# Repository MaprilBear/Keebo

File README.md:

# Keebo - WIP
Successor/65% version of the [Keebi](https://github.com/MaprilBear/Keebi)

## Changes from the Keebi
- Slighty larger IPS display
- "63%" Layout
  - 65% but without INS/DEL, HOME/END, and PG UP/DN buttons
- Per-key RGB Lighting
- Volume Knob
- Improved Firmware
  - Programmable Macros
  - Media and Volume Controls

## Credits
Iterated upon from the [Keebi](https://github.com/MaprilBear/Keebi), a student project for UT Austin's ECE 445L class

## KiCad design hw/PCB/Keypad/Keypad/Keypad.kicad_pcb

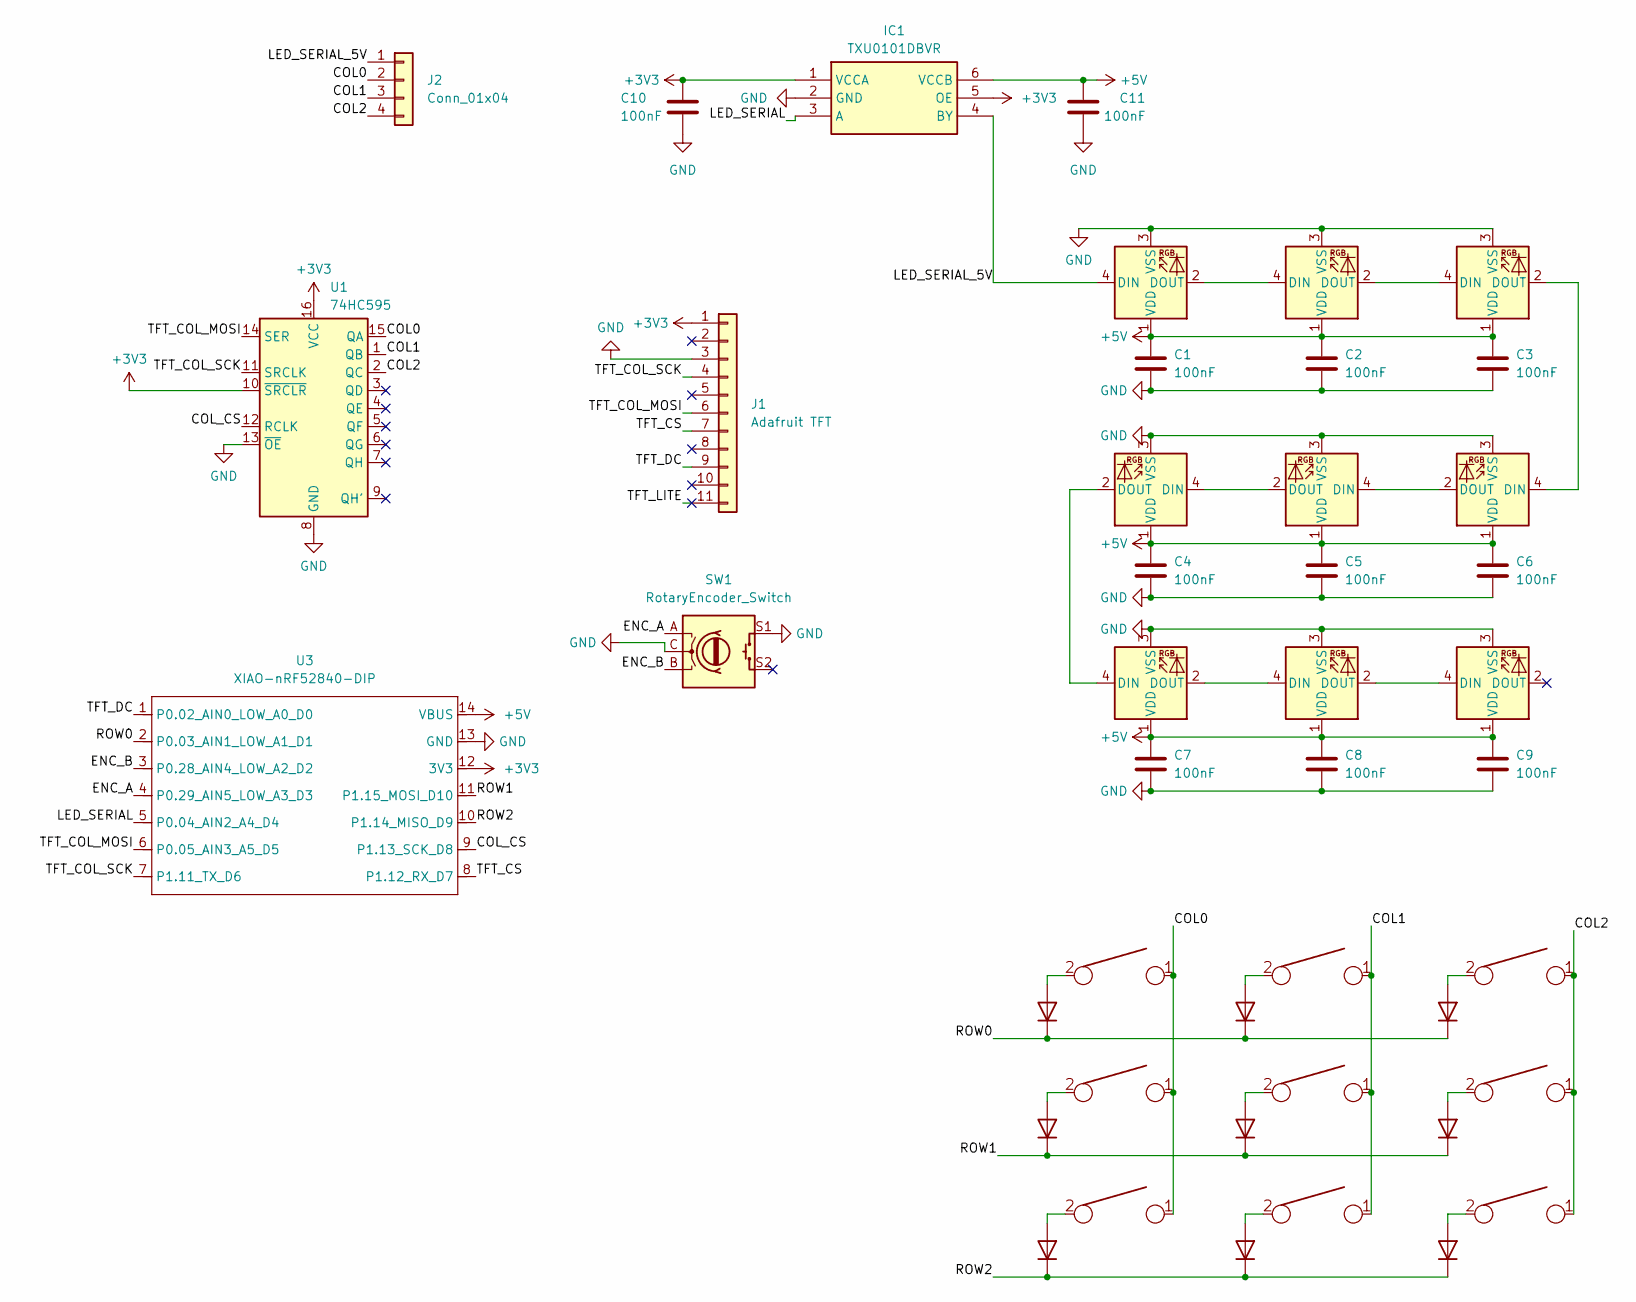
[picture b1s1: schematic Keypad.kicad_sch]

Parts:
C1, C2, C3, C4, C5, C6, C7, C8, C9, C10, C11: 100nF; C_0603_1608Metric
D1, D2, D3, D4, D5, D6, D7, D8, D9: 1N4448W; D_SOD-123
IC1: TXU0101DBVR; SOT-23-6; Mouser Part Number 595-TXU0101DCKR
J1: Adafruit TFT; Adafruit_1.47_TFT_Round_Rect
J2: Conn_01x04; PinHeader_1x04_P2.54mm_Vertical
K1, K2, K3, K4, K5, K6, K7, K8, K9: KEYSW; MX-Hotswap-1U
LED1, LED2, LED3, LED4, LED5, LED6, LED7, LED8, LED9: SK6812-MINI-E
SW1: RotaryEncoder_Switch; RollerEncoder_Panasonic_EVQWGD001
U1: 74HC595; TSSOP-16_4.4x5mm_P0.65mm
U3: XIAO-nRF52840-DIP

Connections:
+3V3: C10.1, IC1.1 (VCCA), IC1.5 (OE), J1.1, U1.10 (~SRCLR), U1.16 (VCC), U3.12 (3V3)
+5V: C1.1, C2.1, C3.1, C4.1, C5.1, C6.1, C7.1, C8.1, C9.1, C11.1, IC1.6 (VCCB), LED1.1 (VDD), LED2.1 (VDD), LED3.1 (VDD), LED4.1 (VDD), LED5.1 (VDD), LED6.1 (VDD), LED7.1 (VDD), LED8.1 (VDD), LED9.1 (VDD), U3.14 (VBUS)
/COL0: J2.2, K1.1, K6.1, K7.1, U1.15 (QA)
/COL1: J2.3, K2.1, K5.1, K8.1, U1.1 (QB)
/COL2: J2.4, K3.1, K4.1, K9.1, U1.2 (QC)
/COL_CS: U1.12 (RCLK), U3.9 (P1.13_SCK_D8)
/ENC_A: SW1.A, U3.4 (P0.29_AIN5_LOW_A3_D3)
/ENC_B: SW1.B, U3.3 (P0.28_AIN4_LOW_A2_D2)
/LED_SERIAL: IC1.3 (A), U3.5 (P0.04_AIN2_A4_D4)
/LED_SERIAL_5V: IC1.4 (BY), J2.1, LED1.4 (DIN)
/ROW0: D1.1 (K), D2.1 (K), D3.1 (K), U3.2 (P0.03_AIN1_LOW_A1_D1)
/ROW1: D4.1 (K), D5.1 (K), D6.1 (K), U3.11 (P1.15_MOSI_D10)
/ROW2: D7.1 (K), D8.1 (K), D9.1 (K), U3.10 (P1.14_MISO_D9)
/TFT_COL_MOSI: J1.6, U1.14 (SER), U3.6 (P0.05_AIN3_A5_D5)
/TFT_COL_SCK: J1.4, U1.11 (SRCLK), U3.7 (P1.11_TX_D6)
/TFT_CS: J1.7, U3.8 (P1.12_RX_D7)
/TFT_DC: J1.9, U3.1 (P0.02_AIN0_LOW_A0_D0)
/TFT_LITE: J1.11
GND: C1.2, C2.2, C3.2, C4.2, C5.2, C6.2, C7.2, C8.2, C9.2, C10.2, C11.2, IC1.2 (GND), J1.3, LED1.3 (VSS), LED2.3 (VSS), LED3.3 (VSS), LED4.3 (VSS), LED5.3 (VSS), LED6.3 (VSS), LED7.3 (VSS), LED8.3 (VSS), LED9.3 (VSS), SW1.C, SW1.S1, U1.8 (GND), U1.13 (~OE), U3.13 (GND)
unnamed: D1.2 (A), K1.2
unnamed: D2.2 (A), K2.2
unnamed: D3.2 (A), K3.2
unnamed: D4.2 (A), K6.2
unnamed: D5.2 (A), K5.2
unnamed: D6.2 (A), K4.2
unnamed: D7.2 (A), K7.2
unnamed: D8.2 (A), K8.2
unnamed: D9.2 (A), K9.2
unnamed: LED1.2 (DOUT), LED2.4 (DIN)
unnamed: LED2.2 (DOUT), LED3.4 (DIN)
unnamed: LED3.2 (DOUT), LED6.4 (DIN)
unnamed: LED4.4 (DIN), LED5.2 (DOUT)
unnamed: LED4.2 (DOUT), LED7.4 (DIN)
unnamed: LED5.4 (DIN), LED6.2 (DOUT)
unnamed: LED7.2 (DOUT), LED8.4 (DIN)
unnamed: LED8.2 (DOUT), LED9.4 (DIN)

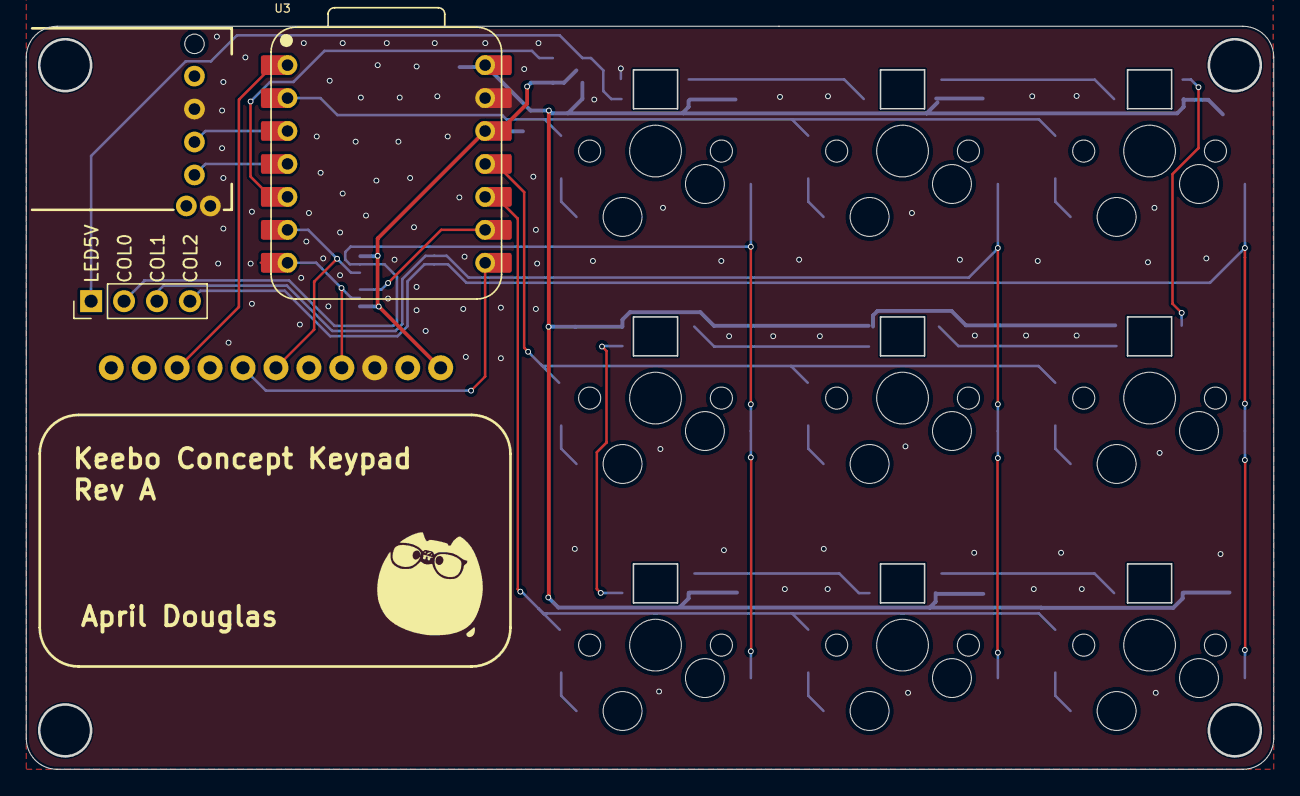
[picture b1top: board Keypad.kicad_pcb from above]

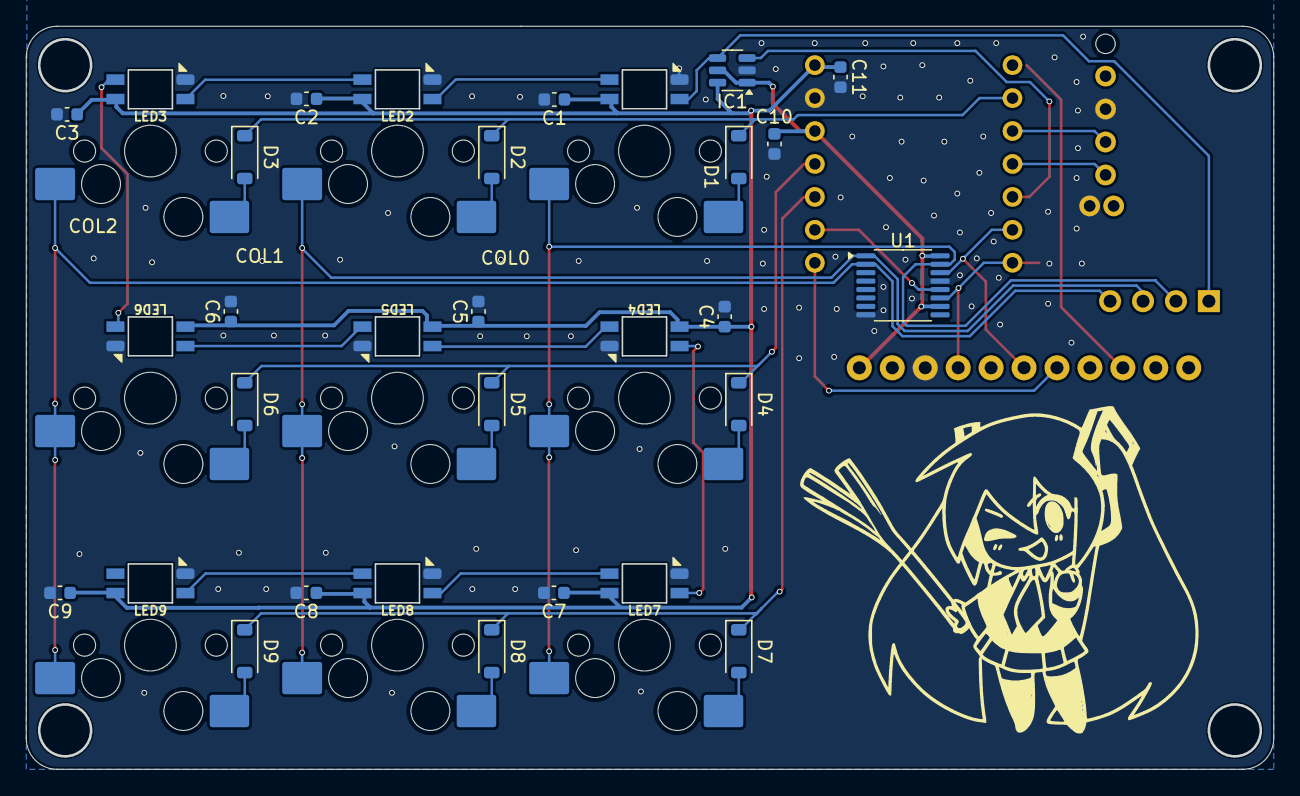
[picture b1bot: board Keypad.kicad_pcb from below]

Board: 2 copper layers, 96.2 x 57.3 mm, 44 parts (31 on the bottom side), 35 nets.

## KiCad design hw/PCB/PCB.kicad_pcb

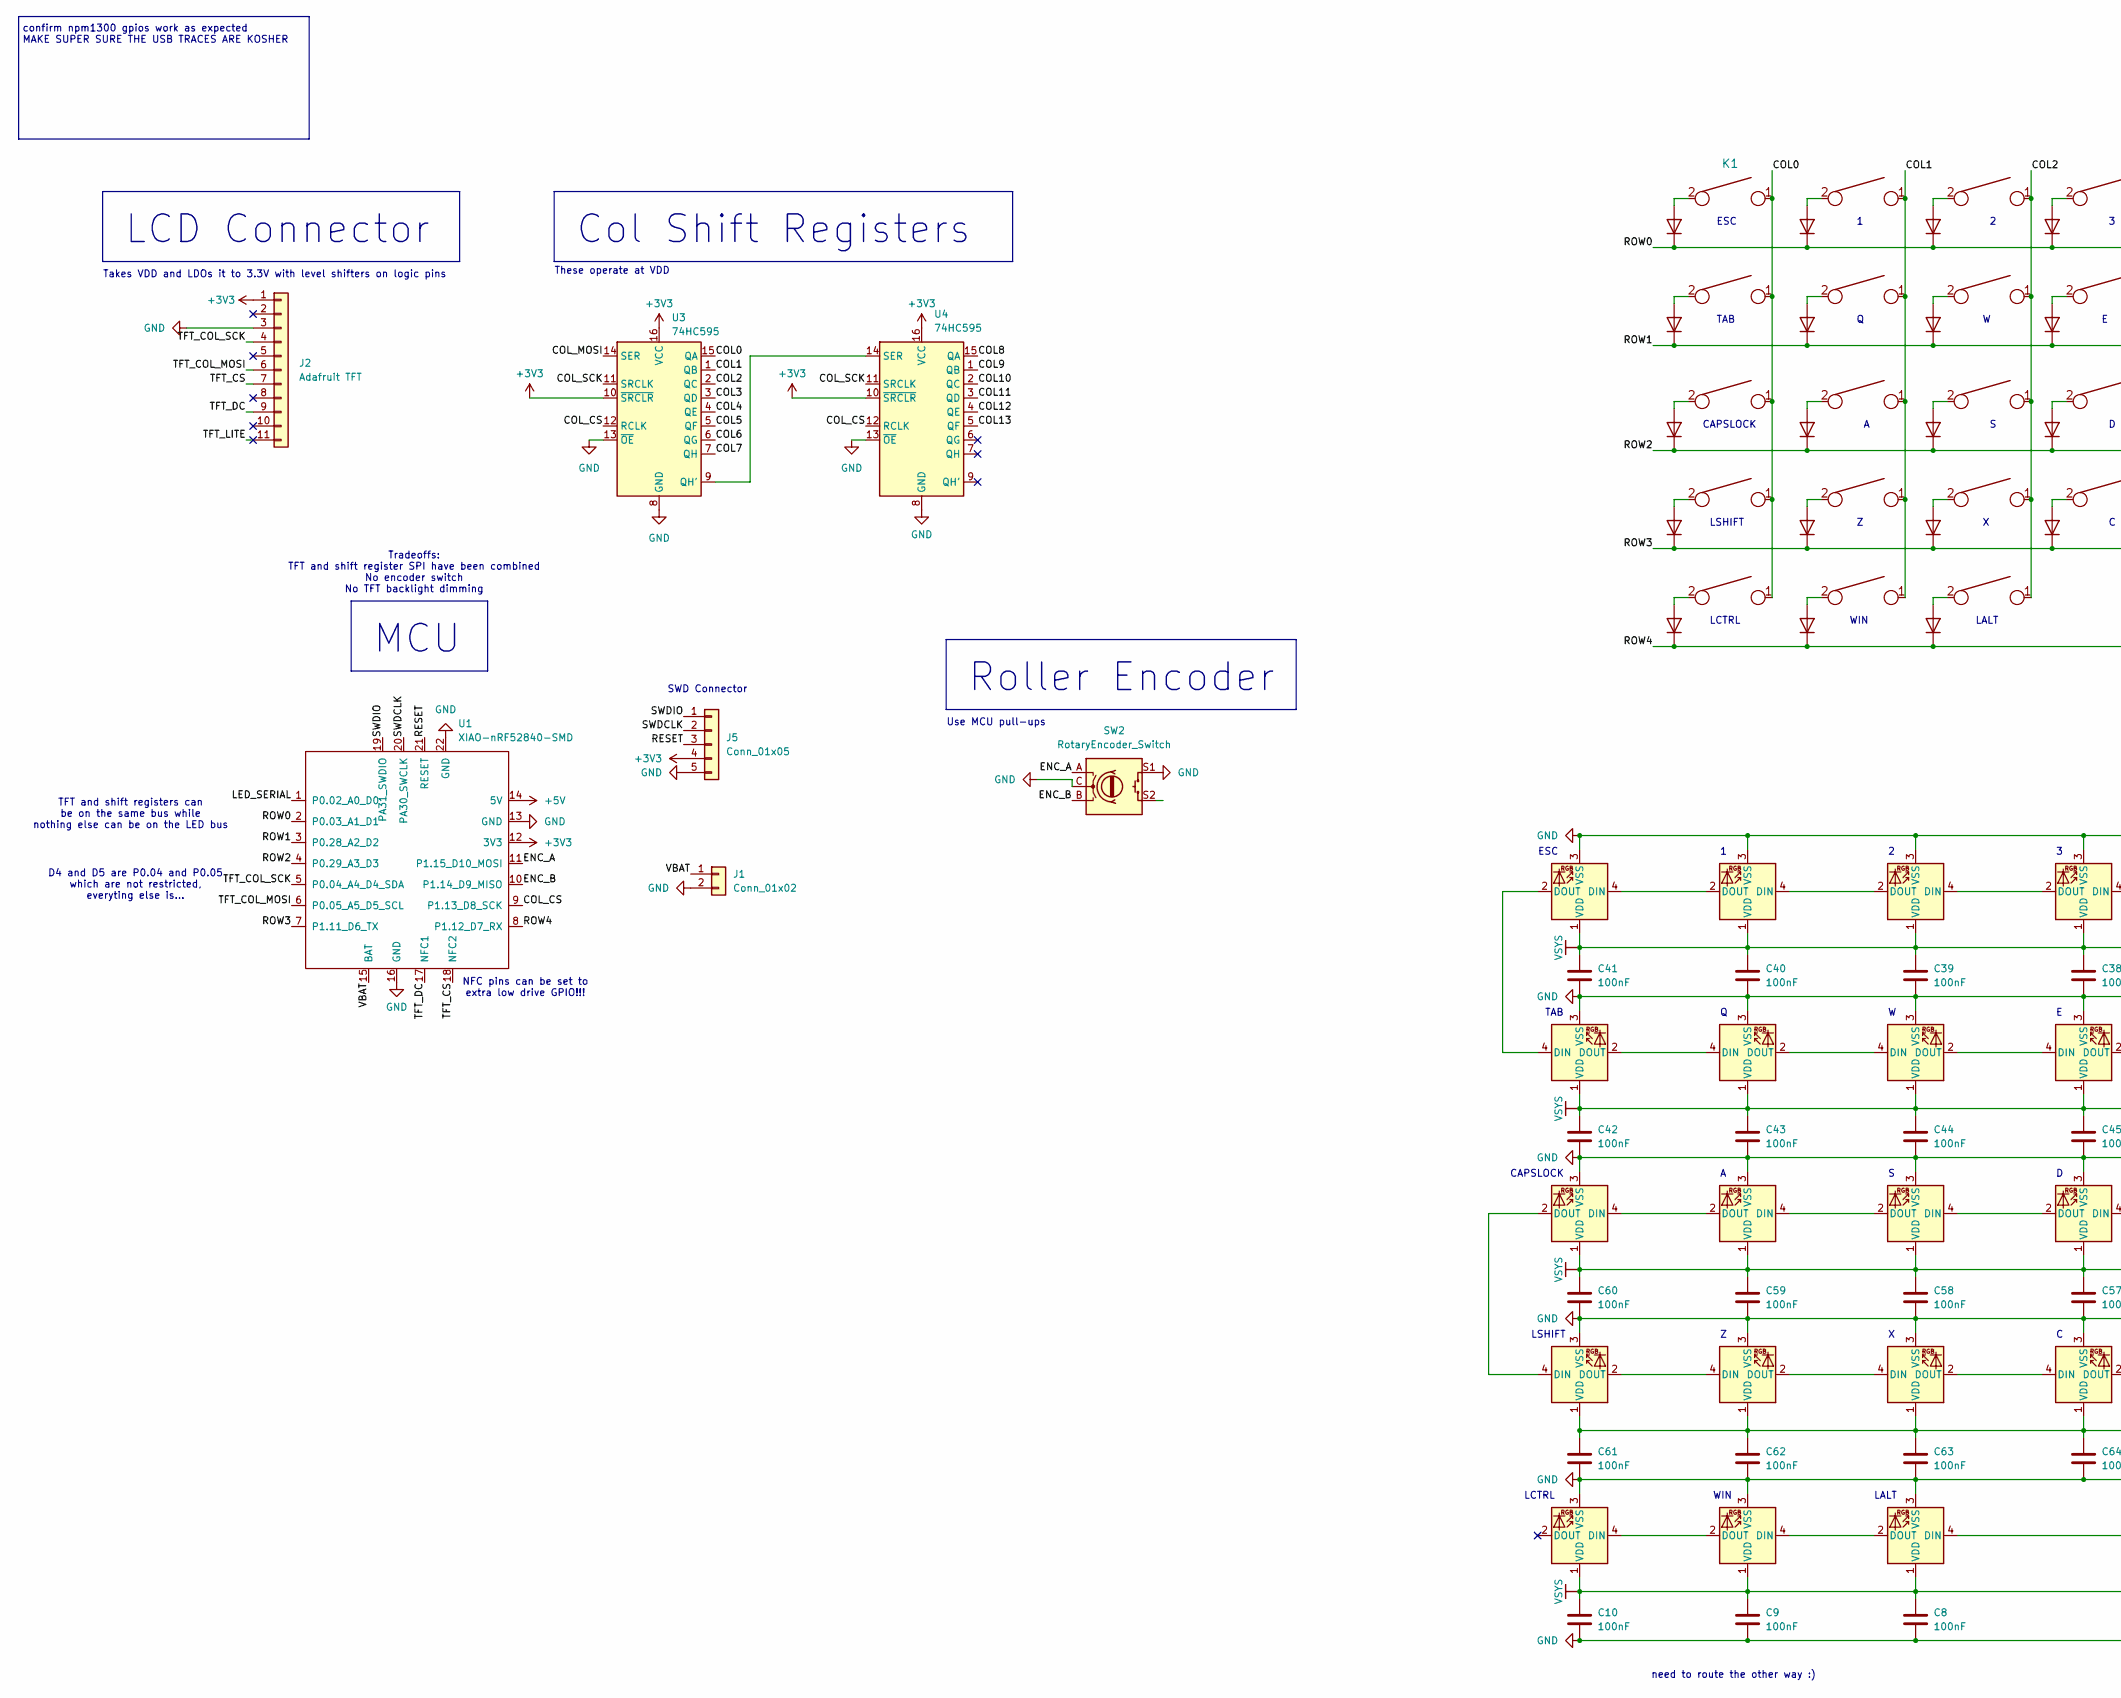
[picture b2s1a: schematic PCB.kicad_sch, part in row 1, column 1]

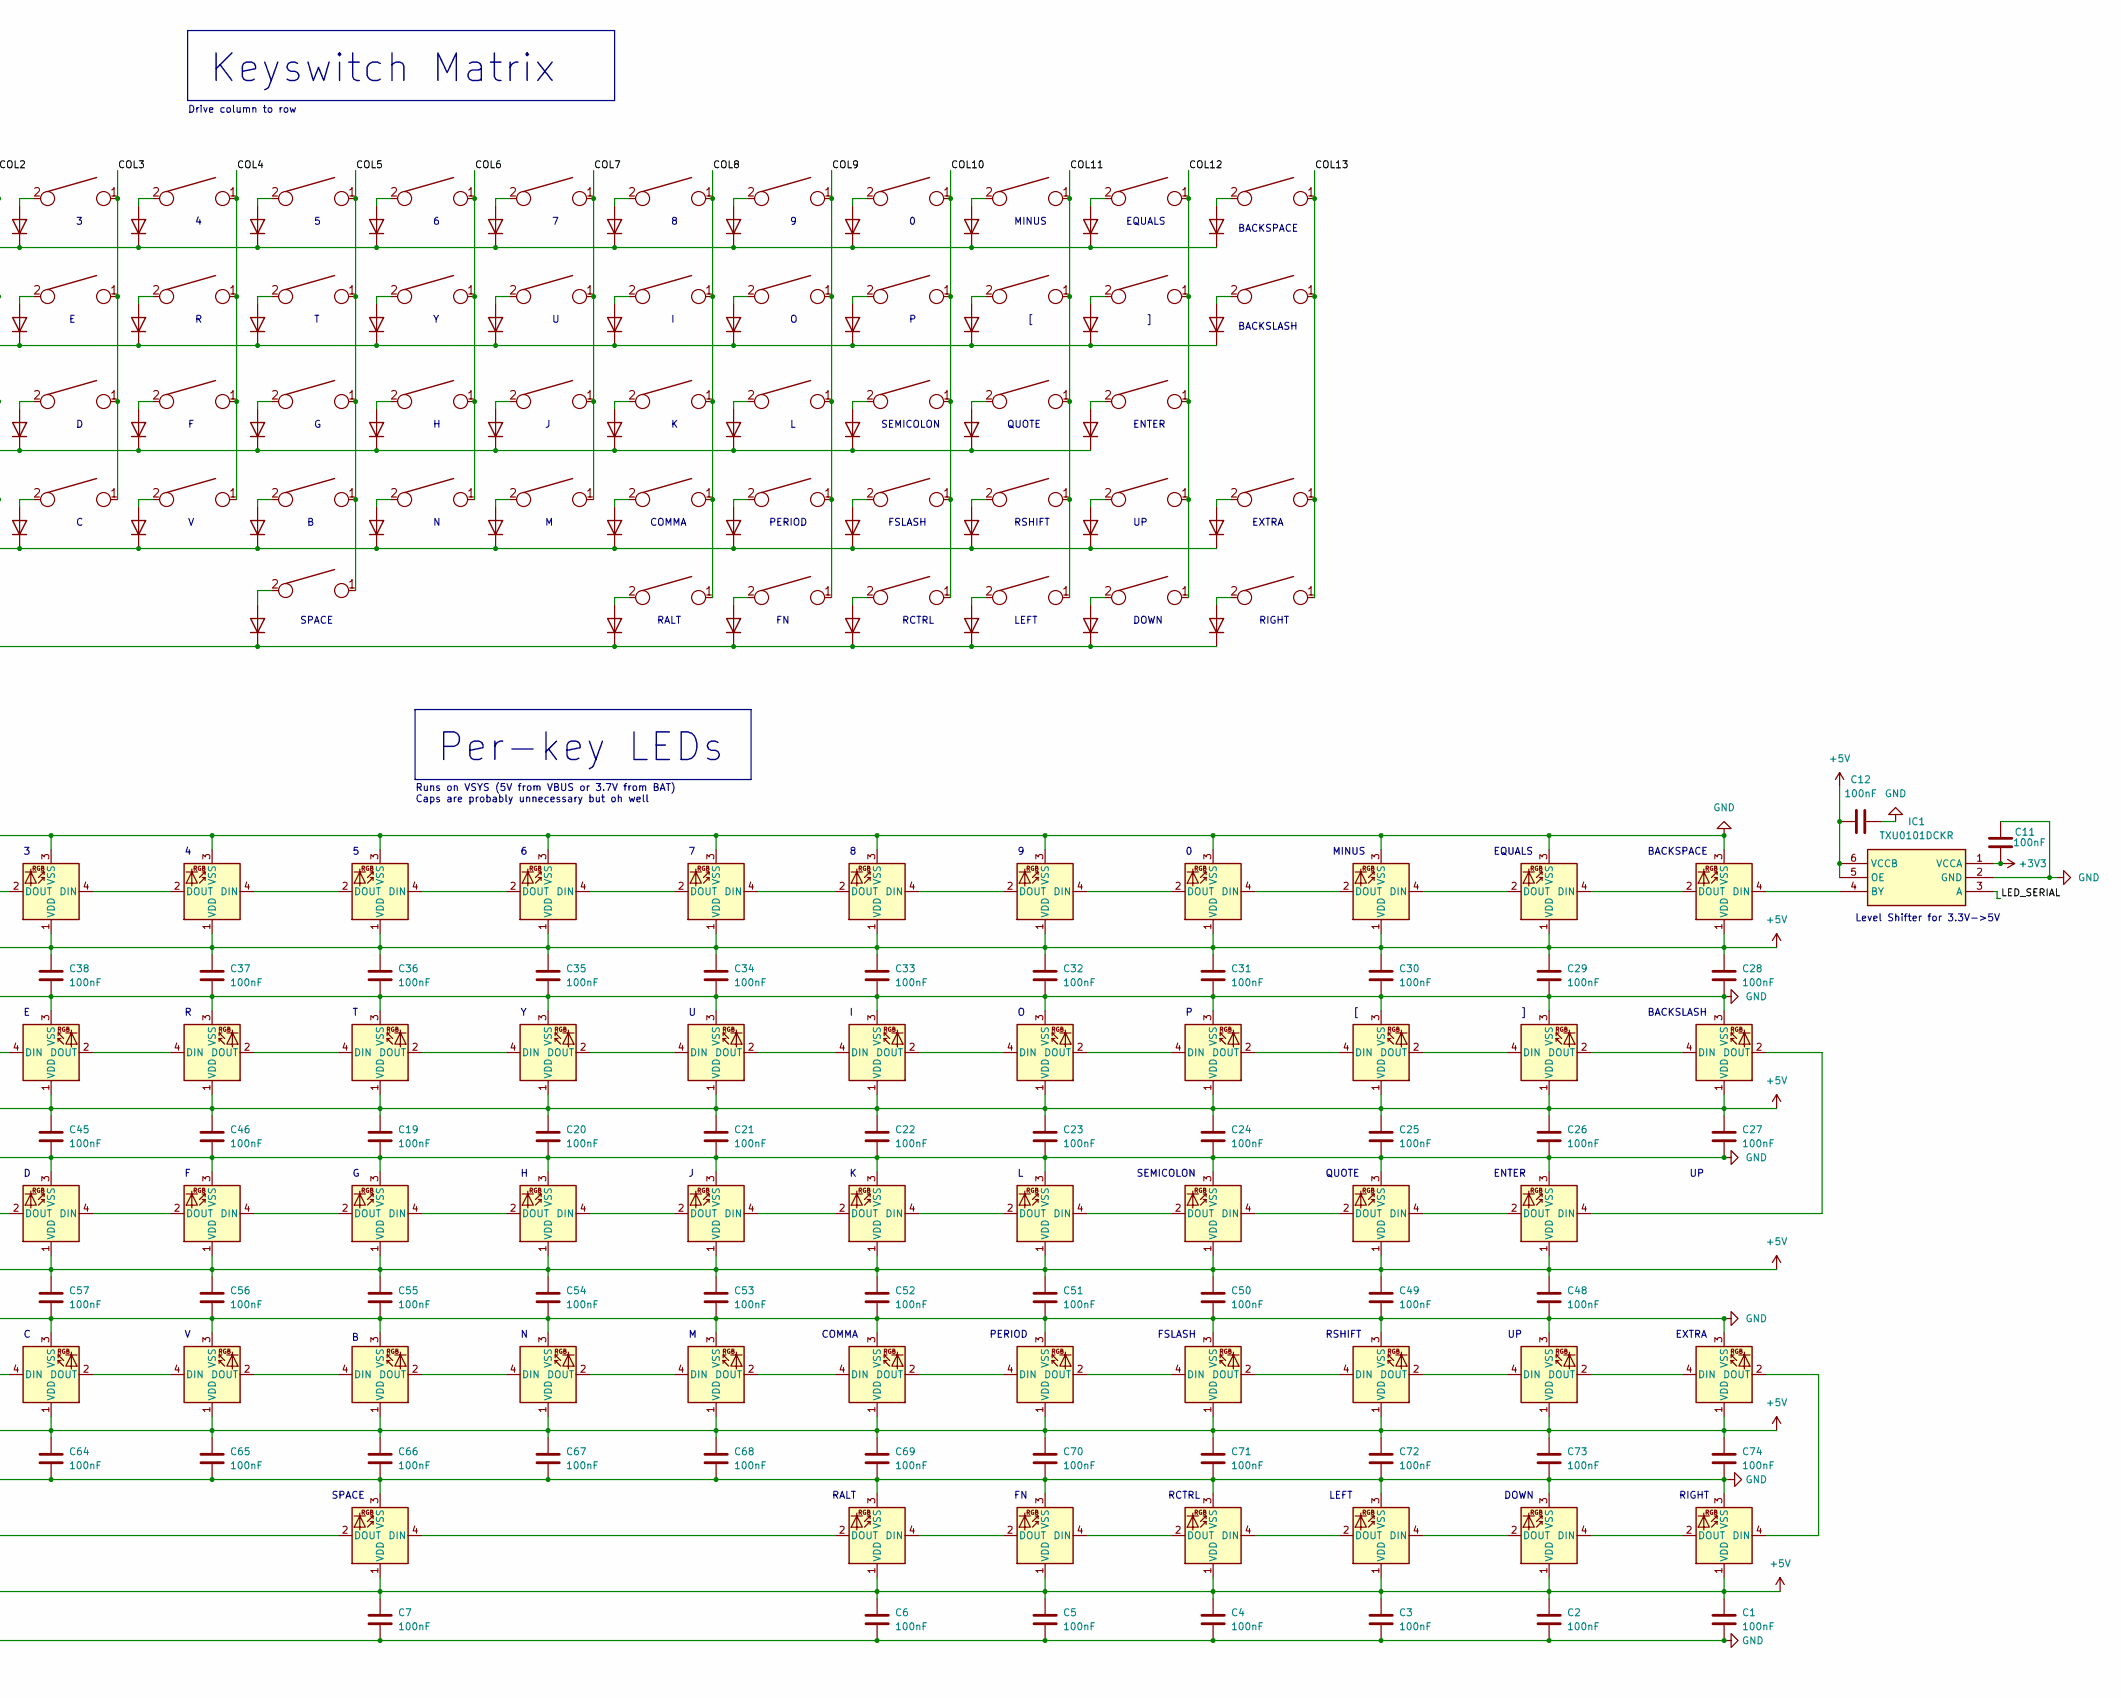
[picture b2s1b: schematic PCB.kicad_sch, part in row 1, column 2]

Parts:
C1, C2, C3, C4, C5, C6, C7, C8, C9, C10, C11, C12, C19, C20, C21, C22, C23, C24, C25, C26, C27, C28, C29, C30, C31, C32, C33, C34, C35, C36, C37, C38, C39, C40, C41, C42, C43, C44, C45, C46, C48, C49, C50, C51, C52, C53, C54, C55, C56, C57, C58, C59, C60, C61, C62, C63, C64, C65, C66, C67, C68, C69, C70, C71, C72, C73, C74: 100nF; C_0603_1608Metric
D1, D2, D3, D4, D5, D6, D7, D8, D9, D10, D11, D12, D13, D14, D15, D16, D17, D18, D19, D20, D21, D22, D23, D24, D25, D26, D27, D28, D29, D31, D32, D33, D34, D35, D36, D37, D38, D39, D40, D41, D42, D43, D46, D47, D48, D49, D50, D51, D52, D53, D54, D55, D56, D57, D58, D59, D61, D62, D63, D64, D65, D66, D67, D68, D69: 1N4448W; D_SOD-123
IC1: TXU0101DCKR; SOT65P210X110-6N; Mouser Part Number 595-TXU0101DCKR
J1: Conn_01x02; PinHeader_1x02_P2.54mm_Vertical
J2: Adafruit TFT; Adafruit_1.47_TFT_Round_Rect
J5: Conn_01x05; PinHeader_1x05_P2.54mm_Vertical
K1, K2, K3, K4, K5, K6, K7, K8, K9, K10, K11, K12, K13, K17, K18, K19, K20, K21, K22, K23, K24, K25, K26, K27, K28, K32, K33, K34, K35, K36, K37, K38, K39, K40, K41, K42, K47, K48, K49, K50, K51, K52, K53, K54, K55, K56, K58, K59, K67, K68, K69: KEYSW; MX-Hotswap-1U
K14: KEYSW; MX-Hotswap-2U
K15, K61, K62, K63, K65, K66: KEYSW; MX-Hotswap-1.25U
K16, K29: KEYSW; MX-Hotswap-1.5U
K31: KEYSW; MX-Hotswap-1.75U
K43, K46: KEYSW; MX-Hotswap-2.25U
K57: KEYSW; MX-Hotswap-2.75U
K64: KEYSW; MX-Hotswap-6.25U
LED1, LED2, LED3, LED4, LED5, LED6, LED7, LED8, LED9, LED10, LED11, LED12, LED13, LED14, LED15, LED16, LED17, LED18, LED19, LED20, LED21, LED22, LED23, LED24, LED25, LED26, LED27, LED28, LED29, LED30, LED31, LED32, LED33, LED34, LED35, LED36, LED37, LED38, LED39, LED40, LED41, LED42, LED43, LED46, LED47, LED48, LED49, LED50, LED51, LED52, LED53, LED54, LED55, LED56, LED57, LED58, LED59, LED61, LED62, LED63, LED64, LED65, LED66, LED67, LED68: SK6812-MINI-E
SW2: RotaryEncoder_Switch; RollerEncoder_Panasonic_EVQWGD001
U1: XIAO-nRF52840-SMD
U3, U4: 74HC595; TSSOP-16_4.4x5mm_P0.65mm

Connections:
+3V3: C11.2, IC1.1 (VCCA), J2.1, J5.4, U1.12 (3V3), U3.10 (~SRCLR), U3.16 (VCC), U4.10 (~SRCLR), U4.16 (VCC)
+5V: C1.1, C2.1, C3.1, C4.1, C5.1, C6.1, C7.1, C8.1, C9.1, C10.1, C12.2, C19.1, C20.1, C21.1, C22.1, C23.1, C24.1, C25.1, C26.1, C27.1, C28.1, C29.1, C30.1, C31.1, C32.1, C33.1, C34.1, C35.1, C36.1, C37.1, C38.1, C39.1, C40.1, C41.1, C42.1, C43.1, C44.1, C45.1, C46.1, C48.1, C49.1, C50.1, C51.1, C52.1, C53.1, C54.1, C55.1, C56.1, C57.1, C58.1, C59.1, C60.1, C61.1, C62.1, C63.1, C64.1, C65.1, C66.1, C67.1, C68.1, C69.1, C70.1, C71.1, C72.1, C73.1, C74.1, IC1.5 (OE), IC1.6 (VCCB), LED1.1 (VDD), LED2.1 (VDD), LED3.1 (VDD), LED4.1 (VDD), LED5.1 (VDD), LED6.1 (VDD), LED7.1 (VDD), LED8.1 (VDD), LED9.1 (VDD), LED10.1 (VDD), LED11.1 (VDD), LED12.1 (VDD), LED13.1 (VDD), LED14.1 (VDD), LED15.1 (VDD), LED16.1 (VDD), LED17.1 (VDD), LED18.1 (VDD), LED19.1 (VDD), LED20.1 (VDD), LED21.1 (VDD), LED22.1 (VDD), LED23.1 (VDD), LED24.1 (VDD), LED25.1 (VDD), LED26.1 (VDD), LED27.1 (VDD), LED28.1 (VDD), LED29.1 (VDD), LED30.1 (VDD), LED31.1 (VDD), LED32.1 (VDD), LED33.1 (VDD), LED34.1 (VDD), LED35.1 (VDD), LED36.1 (VDD), LED37.1 (VDD), LED38.1 (VDD), LED39.1 (VDD), LED40.1 (VDD), LED41.1 (VDD), LED42.1 (VDD), LED43.1 (VDD), LED46.1 (VDD), LED47.1 (VDD), LED48.1 (VDD), LED49.1 (VDD), LED50.1 (VDD), LED51.1 (VDD), LED52.1 (VDD), LED53.1 (VDD), LED54.1 (VDD), LED55.1 (VDD), LED56.1 (VDD), LED57.1 (VDD), LED58.1 (VDD), LED59.1 (VDD), LED61.1 (VDD), LED62.1 (VDD), LED63.1 (VDD), LED64.1 (VDD), LED65.1 (VDD)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
/COL0: K1.1, K16.1, K31.1, K46.1, K61.1, U3.15 (QA)
/COL1: K2.1, K17.1, K32.1, K47.1, K62.1, U3.1 (QB)
/COL2: K3.1, K18.1, K33.1, K48.1, K63.1, U3.2 (QC)
/COL3: K4.1, K19.1, K34.1, K49.1, U3.3 (QD)
/COL4: K5.1, K20.1, K35.1, K50.1, U3.4 (QE)
/COL5: K6.1, K21.1, K36.1, K51.1, K64.1, U3.5 (QF)
/COL6: K7.1, K22.1, K37.1, K52.1, U3.6 (QG)
/COL7: K8.1, K23.1, K38.1, K53.1, U3.7 (QH)
/COL8: K9.1, K15.1, K24.1, K39.1, K54.1, U4.15 (QA)
/COL9: K10.1, K25.1, K40.1, K55.1, K65.1, U4.1 (QB)
/COL10: K11.1, K26.1, K41.1, K56.1, K66.1, U4.2 (QC)
/COL11: K12.1, K27.1, K42.1, K57.1, K67.1, U4.3 (QD)
/COL12: K13.1, K28.1, K43.1, K58.1, K68.1, U4.4 (QE)
/COL13: K14.1, K29.1, K59.1, K69.1, U4.5 (QF)
/COL_CS: U1.9 (P1.13_D8_SCK), U3.12 (RCLK), U4.12 (RCLK)
/COL_MOSI: U3.14 (SER)
/COL_SCK: U3.11 (SRCLK), U4.11 (SRCLK)
/ENC_A: SW2.A, U1.11 (P1.15_D10_MOSI)
/ENC_B: SW2.B, U1.10 (P1.14_D9_MISO)
/LED_SERIAL: IC1.3 (A), U1.1 (P0.02_A0_D0)
/RESET: J5.3, U1.21 (RESET)
/ROW0: D1.1 (K), D2.1 (K), D3.1 (K), D4.1 (K), D5.1 (K), D6.1 (K), D7.1 (K), D8.1 (K), D9.1 (K), D10.1 (K), D11.1 (K), D12.1 (K), D13.1 (K), D14.1 (K), U1.2 (P0.03_A1_D1)
/ROW1: D16.1 (K), D17.1 (K), D18.1 (K), D19.1 (K), D20.1 (K), D21.1 (K), D22.1 (K), D23.1 (K), D24.1 (K), D25.1 (K), D26.1 (K), D27.1 (K), D28.1 (K), D29.1 (K), U1.3 (P0.28_A2_D2)
/ROW2: D31.1 (K), D32.1 (K), D33.1 (K), D34.1 (K), D35.1 (K), D36.1 (K), D37.1 (K), D38.1 (K), D39.1 (K), D40.1 (K), D41.1 (K), D42.1 (K), D43.1 (K), U1.4 (P0.29_A3_D3)
/ROW3: D46.1 (K), D47.1 (K), D48.1 (K), D49.1 (K), D50.1 (K), D51.1 (K), D52.1 (K), D53.1 (K), D54.1 (K), D55.1 (K), D56.1 (K), D57.1 (K), D58.1 (K), D59.1 (K), U1.7 (P1.11_D6_TX)
/ROW4: D15.1 (K), D61.1 (K), D62.1 (K), D63.1 (K), D64.1 (K), D65.1 (K), D66.1 (K), D67.1 (K), D68.1 (K), D69.1 (K), U1.8 (P1.12_D7_RX)
/SWDCLK: J5.2, U1.20 (PA30_SWCLK)
/SWDIO: J5.1, U1.19 (PA31_SWDIO)
/TFT_COL_MOSI: J2.6, U1.6 (P0.05_A5_D5_SCL)
/TFT_COL_SCK: J2.4, U1.5 (P0.04_A4_D4_SDA)
/TFT_CS: J2.7, U1.18 (NFC2)
/TFT_DC: J2.9, U1.17 (NFC1)
/TFT_LITE: J2.11
/VBAT: J1.1, U1.15 (BAT)
GND: C1.2, C2.2, C3.2, C4.2, C5.2, C6.2, C7.2, C8.2, C9.2, C10.2, C11.1, C12.1, C19.2, C20.2, C21.2, C22.2, C23.2, C24.2, C25.2, C26.2, C27.2, C28.2, C29.2, C30.2, C31.2, C32.2, C33.2, C34.2, C35.2, C36.2, C37.2, C38.2, C39.2, C40.2, C41.2, C42.2, C43.2, C44.2, C45.2, C46.2, C48.2, C49.2, C50.2, C51.2, C52.2, C53.2, C54.2, C55.2, C56.2, C57.2, C58.2, C59.2, C60.2, C61.2, C62.2, C63.2, C64.2, C65.2, C66.2, C67.2, C68.2, C69.2, C70.2, C71.2, C72.2, C73.2, C74.2, IC1.2 (GND), J1.2, J2.3, J5.5, LED1.3 (VSS), LED2.3 (VSS), LED3.3 (VSS), LED4.3 (VSS), LED5.3 (VSS), LED6.3 (VSS), LED7.3 (VSS), LED8.3 (VSS), LED9.3 (VSS), LED10.3 (VSS), LED11.3 (VSS), LED12.3 (VSS), LED13.3 (VSS), LED14.3 (VSS), LED15.3 (VSS), LED16.3 (VSS), LED17.3 (VSS), LED18.3 (VSS), LED19.3 (VSS), LED20.3 (VSS), LED21.3 (VSS), LED22.3 (VSS), LED23.3 (VSS), LED24.3 (VSS), LED25.3 (VSS), LED26.3 (VSS), LED27.3 (VSS), LED28.3 (VSS), LED29.3 (VSS), LED30.3 (VSS), LED31.3 (VSS), LED32.3 (VSS), LED33.3 (VSS), LED34.3 (VSS), LED35.3 (VSS), LED36.3 (VSS), LED37.3 (VSS), LED38.3 (VSS), LED39.3 (VSS), LED40.3 (VSS), LED41.3 (VSS), LED42.3 (VSS), LED43.3 (VSS), LED46.3 (VSS), LED47.3 (VSS), LED48.3 (VSS), LED49.3 (VSS), LED50.3 (VSS), LED51.3 (VSS), LED52.3 (VSS), LED53.3 (VSS), LED54.3 (VSS), LED55.3 (VSS), LED56.3 (VSS), LED57.3 (VSS), LED58.3 (VSS), LED59.3 (VSS), LED61.3 (VSS), LED62.3 (VSS)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
unnamed: D1.2 (A), K1.2
unnamed: D2.2 (A), K2.2
unnamed: D3.2 (A), K3.2
unnamed: D4.2 (A), K4.2
unnamed: D5.2 (A), K5.2
unnamed: D6.2 (A), K6.2
unnamed: D7.2 (A), K7.2
unnamed: D8.2 (A), K8.2
unnamed: D9.2 (A), K9.2
unnamed: D10.2 (A), K10.2
unnamed: D11.2 (A), K11.2
unnamed: D12.2 (A), K12.2
unnamed: D13.2 (A), K13.2
unnamed: D14.2 (A), K14.2
unnamed: D15.2 (A), K15.2
unnamed: D16.2 (A), K16.2
unnamed: D17.2 (A), K17.2
unnamed: D18.2 (A), K18.2
unnamed: D19.2 (A), K19.2
unnamed: D20.2 (A), K20.2
unnamed: D21.2 (A), K21.2
unnamed: D22.2 (A), K22.2
unnamed: D23.2 (A), K23.2
unnamed: D24.2 (A), K24.2
unnamed: D25.2 (A), K25.2
unnamed: D26.2 (A), K26.2
unnamed: D27.2 (A), K27.2
unnamed: D28.2 (A), K28.2
unnamed: D29.2 (A), K29.2
unnamed: D31.2 (A), K31.2
unnamed: D32.2 (A), K32.2
unnamed: D33.2 (A), K33.2
unnamed: D34.2 (A), K34.2
unnamed: D35.2 (A), K35.2
unnamed: D36.2 (A), K36.2
unnamed: D37.2 (A), K37.2
unnamed: D38.2 (A), K38.2
unnamed: D39.2 (A), K39.2
unnamed: D40.2 (A), K40.2
unnamed: D41.2 (A), K41.2
unnamed: D42.2 (A), K42.2
unnamed: D43.2 (A), K43.2
unnamed: D46.2 (A), K46.2
unnamed: D47.2 (A), K47.2
unnamed: D48.2 (A), K48.2
unnamed: D49.2 (A), K49.2
unnamed: D50.2 (A), K50.2
unnamed: D51.2 (A), K51.2
unnamed: D52.2 (A), K52.2
unnamed: D53.2 (A), K53.2
unnamed: D54.2 (A), K54.2
unnamed: D55.2 (A), K55.2
unnamed: D56.2 (A), K56.2
unnamed: D57.2 (A), K57.2
unnamed: D58.2 (A), K58.2
unnamed: D59.2 (A), K59.2
unnamed: D61.2 (A), K61.2
unnamed: D62.2 (A), K62.2
unnamed: D63.2 (A), K63.2
unnamed: D64.2 (A), K64.2
unnamed: D65.2 (A), K65.2
unnamed: D66.2 (A), K66.2
unnamed: D67.2 (A), K67.2
unnamed: D68.2 (A), K68.2
unnamed: D69.2 (A), K69.2
unnamed: IC1.4 (BY), LED14.4 (DIN)
unnamed: LED1.4 (DIN), LED2.2 (DOUT)
unnamed: LED1.2 (DOUT), LED16.4 (DIN)
unnamed: LED2.4 (DIN), LED3.2 (DOUT)
unnamed: LED3.4 (DIN), LED4.2 (DOUT)
unnamed: LED4.4 (DIN), LED5.2 (DOUT)
unnamed: LED5.4 (DIN), LED6.2 (DOUT)
unnamed: LED6.4 (DIN), LED7.2 (DOUT)
unnamed: LED7.4 (DIN), LED8.2 (DOUT)
unnamed: LED8.4 (DIN), LED9.2 (DOUT)
unnamed: LED10.4 (DIN), LED11.2 (DOUT)
unnamed: LED9.4 (DIN), LED10.2 (DOUT)
unnamed: LED11.4 (DIN), LED12.2 (DOUT)
unnamed: LED12.4 (DIN), LED13.2 (DOUT)
unnamed: LED13.4 (DIN), LED14.2 (DOUT)
unnamed: LED15.4 (DIN), LED30.2 (DOUT)
unnamed: LED15.2 (DOUT), LED68.4 (DIN)
unnamed: LED16.2 (DOUT), LED17.4 (DIN)
unnamed: LED17.2 (DOUT), LED18.4 (DIN)
unnamed: LED18.2 (DOUT), LED19.4 (DIN)
unnamed: LED19.2 (DOUT), LED20.4 (DIN)
unnamed: LED20.2 (DOUT), LED21.4 (DIN)
unnamed: LED21.2 (DOUT), LED22.4 (DIN)
unnamed: LED22.2 (DOUT), LED23.4 (DIN)
unnamed: LED23.2 (DOUT), LED24.4 (DIN)
unnamed: LED24.2 (DOUT), LED25.4 (DIN)
unnamed: LED25.2 (DOUT), LED26.4 (DIN)
unnamed: LED26.2 (DOUT), LED27.4 (DIN)
unnamed: LED27.2 (DOUT), LED28.4 (DIN)
unnamed: LED28.2 (DOUT), LED29.4 (DIN)
unnamed: LED29.2 (DOUT), LED43.4 (DIN)
unnamed: LED30.4 (DIN), LED59.2 (DOUT)
unnamed: LED31.4 (DIN), LED32.2 (DOUT)
unnamed: LED31.2 (DOUT), LED46.4 (DIN)
unnamed: LED32.4 (DIN), LED33.2 (DOUT)
unnamed: LED33.4 (DIN), LED34.2 (DOUT)
unnamed: LED34.4 (DIN), LED35.2 (DOUT)
unnamed: LED35.4 (DIN), LED36.2 (DOUT)
unnamed: LED36.4 (DIN), LED37.2 (DOUT)
unnamed: LED37.4 (DIN), LED38.2 (DOUT)
unnamed: LED38.4 (DIN), LED39.2 (DOUT)
unnamed: LED39.4 (DIN), LED40.2 (DOUT)
unnamed: LED40.4 (DIN), LED41.2 (DOUT)
unnamed: LED41.4 (DIN), LED42.2 (DOUT)
unnamed: LED42.4 (DIN), LED43.2 (DOUT)
unnamed: LED46.2 (DOUT), LED47.4 (DIN)
unnamed: LED47.2 (DOUT), LED48.4 (DIN)
unnamed: LED48.2 (DOUT), LED49.4 (DIN)
unnamed: LED49.2 (DOUT), LED50.4 (DIN)
unnamed: LED50.2 (DOUT), LED51.4 (DIN)
unnamed: LED51.2 (DOUT), LED52.4 (DIN)
unnamed: LED52.2 (DOUT), LED53.4 (DIN)
unnamed: LED53.2 (DOUT), LED54.4 (DIN)
unnamed: LED54.2 (DOUT), LED55.4 (DIN)
unnamed: LED55.2 (DOUT), LED56.4 (DIN)
unnamed: LED56.2 (DOUT), LED57.4 (DIN)
unnamed: LED57.2 (DOUT), LED58.4 (DIN)
unnamed: LED58.2 (DOUT), LED59.4 (DIN)
unnamed: LED61.4 (DIN), LED62.2 (DOUT)
unnamed: LED62.4 (DIN), LED63.2 (DOUT)
unnamed: LED63.4 (DIN), LED64.2 (DOUT)
unnamed: LED64.4 (DIN), LED65.2 (DOUT)
unnamed: LED65.4 (DIN), LED66.2 (DOUT)
unnamed: LED66.4 (DIN), LED67.2 (DOUT)
unnamed: LED67.4 (DIN), LED68.2 (DOUT)
unnamed: U3.9 (QH'), U4.14 (SER)

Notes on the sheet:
Col Shift Registers
LCD Connector
Per-key LEDs
Keyswitch Matrix
Roller Encoder
MCU
LALT
TAB
CAPSLOCK
RIGHT
RALT
Runs on VSYS (5V from VBUS or 3.7V from BAT) Caps are probably unnecessary but oh well
BACKSPACE
ENTER
LEFT
RSHIFT
QUOTE
FSLASH
confirm npm1300 gpios work as expected MAKE SUPER SURE THE USB TRACES ARE KOSHER
SPACE
need to route the other way :)
EQUALS
COMMA
ESC
PERIOD
LSHIFT
D4 and D5 are P0.04 and P0.05 which are not restricted, everyting else is...
BACKSLASH
NFC pins can be set to extra low drive GPIO!!!
RCTRL
Tradeoffs: TFT and shift register SPI have been combined No encoder switch No TFT backlight dimming
EXTRA
MINUS
SEMICOLON
WIN
Takes VDD and LDOs it to 3.3V with level shifters on logic pins
Level Shifter for 3.3V->5V
These operate at VDD
DOWN
SWD Connector

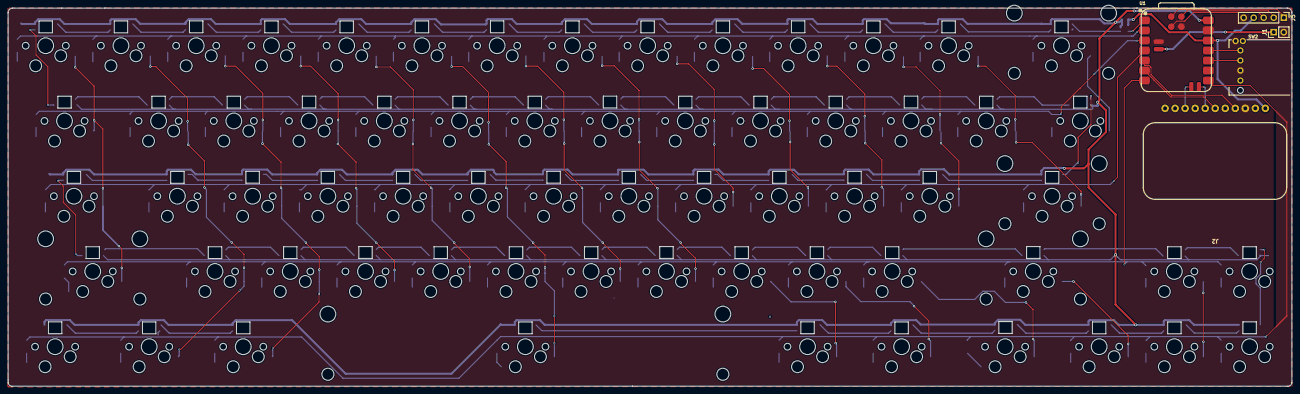
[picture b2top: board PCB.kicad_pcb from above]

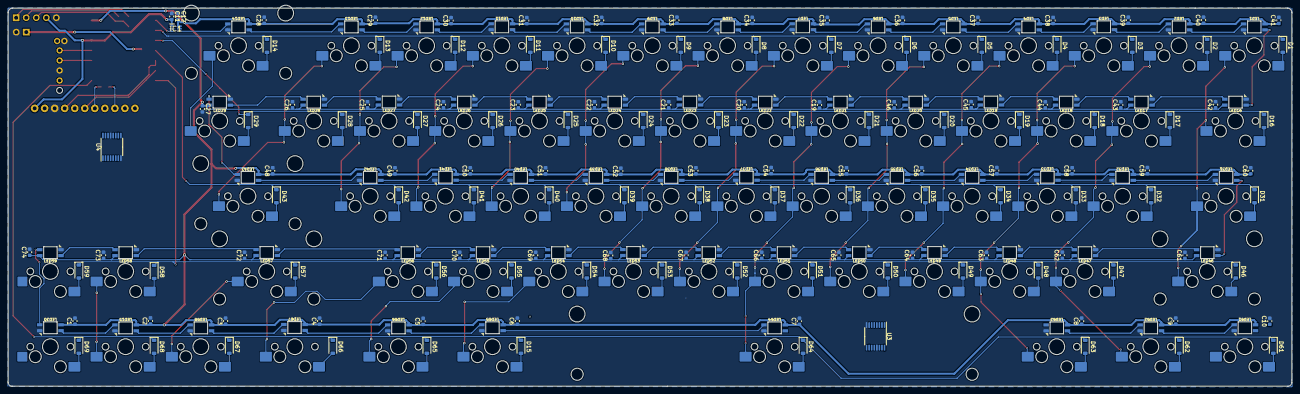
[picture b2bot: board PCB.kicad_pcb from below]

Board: 2 copper layers, 325.0 x 95.7 mm, 270 parts (200 on the bottom side), 166 nets.

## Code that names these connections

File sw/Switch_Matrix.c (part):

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#include "Keyboard.h"
#include <stdbool.h>

#define ROW0 PF3
#define ROW1 PF2
#define ROW2 PF1
#define ROW3 PF0
#define ROW4 PC3 // TDO, must unlock


#define COL0 PC6
#define COL1 PC7
#define COL2 PD7
#define COL3 PE0
#define COL4 PE1
#define COL5 PE2
#define COL6 PE3
#define COL7 PF4
#define COL8 PB7
#define COL9 PB6
#define COL10 PE5
#define COL11 PE4
#define COL12 PB4
#define COL13 PB5

uint8_t modifier = 0;

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  
	
    
      // ROW0 - PF3
			
			// pulse row
			GPIO_PORTF_DATA_R |= (1 << 3);
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      
      Clock_Delay1ms(DELAY);
      
      // ROW1 - PF1
			
			// pulse row
			GPIO_PORTF_DATA_R |= (1 << 1);
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		GPIO_PORTF_DATA_R &= ~(1<<1);
      Clock_Delay1ms(DELAY);

      // ROW2 - PF2
			
			// pulse row
			GPIO_PORTF_DATA_R |= (1 << 2);
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      GPIO_PORTF_DATA_R &= ~(1 << 2);
      Clock_Delay1ms(DELAY);

      // ROW3 - PF0
			
			// pulse row
			GPIO_PORTF_DATA_R |= (1 << 0);
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      GPIO_PORTF_DATA_R &= ~(1 << 0);
      Clock_Delay1ms(DELAY);
                    
      // ROW4 - PC3
			
			// pulse row
			GPIO_PORTC_DATA_R |= (1 << 3);
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  EnableInterrupts();
}

#define ROW0 PF3
#define ROW1 PF2
#define ROW2 PF1
#define ROW3 PF0
#define ROW4 PC3 // TDO, must unlock

void Switch_Init(){

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  GPIO_PORTF_DR8R_R |= (1 << 0) + (1 << 1) + (1 << 2) + (1 << 3);
  GPIO_PORTF_PUR_R &= ~((1 << 0) + (1 << 1) + (1 << 2) + (1 << 3));
  GPIO_PORTF_PDR_R &= ~((1 << 0) + (1 << 1) + (1 << 2) + (1 << 3));
  GPIO_PORTF_DIR_R &= ~(1 << 4); // set col7 to IN
  GPIO_PORTF_PDR_R |= (1 << 4);
	GPIO_PORTF_DEN_R |= 1 + (1 << 1) + (1 << 2) + (1<<3) + (1 << 4);
	
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
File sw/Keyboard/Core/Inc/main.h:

/* USER CODE BEGIN Header */
/**
  ******************************************************************************
  * @file           : main.h
  * @brief          : Header for main.c file.
  *                   This file contains the common defines of the application.
  ******************************************************************************
  * @attention
  *
  * Copyright (c) 2024 STMicroelectronics.
  * All rights reserved.
  *
  * This software is licensed under terms that can be found in the LICENSE file
  * in the root directory of this software component.
  * If no LICENSE file comes with this software, it is provided AS-IS.
  *
  ******************************************************************************
  */
/* USER CODE END Header */

/* Define to prevent recursive inclusion -------------------------------------*/
#ifndef __MAIN_H
#define __MAIN_H

#ifdef __cplusplus
extern "C" {
#endif

/* Includes ------------------------------------------------------------------*/
#include "stm32l5xx_hal.h"

/* Private includes ----------------------------------------------------------*/
/* USER CODE BEGIN Includes */

/* USER CODE END Includes */

/* Exported types ------------------------------------------------------------*/
/* USER CODE BEGIN ET */

/* USER CODE END ET */

/* Exported constants --------------------------------------------------------*/
/* USER CODE BEGIN EC */

extern SPI_HandleTypeDef hspi1;

/* USER CODE END EC */

/* Exported macro ------------------------------------------------------------*/
/* USER CODE BEGIN EM */

/* USER CODE END EM */

void HAL_TIM_MspPostInit(TIM_HandleTypeDef *htim);

/* Exported functions prototypes ---------------------------------------------*/
void Error_Handler(void);

/* USER CODE BEGIN EFP */

/* USER CODE END EFP */

/* Private defines -----------------------------------------------------------*/
#define ROW4_Pin GPIO_PIN_2
#define ROW4_GPIO_Port GPIOE
#define COLMUXC_Pin GPIO_PIN_3
#define COLMUXC_GPIO_Port GPIOE
#define ROW2_Pin GPIO_PIN_4
#define ROW2_GPIO_Port GPIOE
#define COLMUXA_Pin GPIO_PIN_5
#define COLMUXA_GPIO_Port GPIOE
#define COLMUXB_Pin GPIO_PIN_6
#define COLMUXB_GPIO_Port GPIOE
#define User_Button_Pin GPIO_PIN_13
#define User_Button_GPIO_Port GPIOC
#define User_Button_EXTI_IRQn EXTI13_IRQn
#define COLOUTA_Pin GPIO_PIN_5
#define COLOUTA_GPIO_Port GPIOF
#define ROW1_Pin GPIO_PIN_0
#define ROW1_GPIO_Port GPIOC
#define COLOUTB_Pin GPIO_PIN_1
#define COLOUTB_GPIO_Port GPIOG
#define ENC_A_Pin GPIO_PIN_9
#define ENC_A_GPIO_Port GPIOE
#define ENC_B_Pin GPIO_PIN_11
#define ENC_B_GPIO_Port GPIOE
#define TFT_RESET_Pin GPIO_PIN_14
#define TFT_RESET_GPIO_Port GPIOD
#define TFT_DC_Pin GPIO_PIN_15
#define TFT_DC_GPIO_Port GPIOD
#define ENC_SW_Pin GPIO_PIN_8
#define ENC_SW_GPIO_Port GPIOC
#define ROW3_Pin GPIO_PIN_5
#define ROW3_GPIO_Port GPIOD
#define ROW0_Pin GPIO_PIN_6
#define ROW0_GPIO_Port GPIOD
#define LOGIC_TRANS_EN_Pin GPIO_PIN_6
#define LOGIC_TRANS_EN_GPIO_Port GPIOB

/* USER CODE BEGIN Private defines */

/* USER CODE END Private defines */

#ifdef __cplusplus
}
#endif

#endif /* __MAIN_H */

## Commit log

2023-12-02 Files from Stoatboard
2023-12-04 Schematic Block-out
2023-12-04 Slight tweak to keyboard matrix
2023-12-04 LEDs!
2023-12-04 Added macro column and possible rotary encoder
2023-12-05 Every day God abandons me
2023-12-06 Switched to STM32L552RE
2023-12-06 Blocked out connections of the peripherals to the STM32L552
2023-12-07 Lotta Changes, Initial Routing
2024-08-12 I am very good at using version control, BIG UPDATE see desc
    This commit contains version 1 of the daughterboard prototype for the key switch and SK6812-E LED matrix and it already contains a mistake with the floating G2 pin on the row demux :)
2024-08-20 Added basic test program for key matrix
2024-08-21 Working basic firmware!
2024-08-21 Updated polling rate to 1000Hz
2024-08-30 deleted old stuff
2024-08-30 The LEDs work!!
    LEDs use DMA PWM to generate their bit encoding scheme
2024-09-01 Rotated all switches
2024-09-10 Added Function Layer
2024-11-05 Some fixes
2024-12-20 Added display and an attempt at volume control
2024-12-24 add zmk-config subrepo
2024-12-29 Schematic Updates
2024-12-30 "finished" schematic with MinewSemi nRF52840 module
2024-12-31 Routing "done", holy moly
2025-01-01 12/31 Fab Submission
2025-02-07 Added XIAO and ItsyBitsy
2025-02-07 beep boop more changes
2025-02-09 routing
2025-02-14 More routing
2025-02-15 Keebo Proof of Concept Keypad Fab Submission
